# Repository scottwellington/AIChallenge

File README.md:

# Why did the lobster blush?
###### Because the sugar kelp.

---

Welcome to Team 1's GitHub for the AI Challenge!

---

## Getting started

**Step 1**: Grab [Git] tools(https://git-scm.com/book/en/v2/Getting-Started-Installing-Git).

**Step 2**: Clone our repo:

`git clone https://github.com/scottwellington/AIChallenge.git`

## Notes for Team Members: making changes to this repo

Note: this is the most straight-forward and accessible way to use GitHub as a team, but this isn't how you'd typically use it: we are going to simplify the process by avoiding branches, rebase and merge, which are not newbie-friendly.

However, this requires some due diligence that you always pull the latest version before pushing any changes. Important enough to be worth repeating: *Do not push changes to the repo without first pulling the most recent version!*

Navigate to the repo (default `~/AIChallenge`)

**Step 1**: Pull the most recent version of the repo:

`git pull`

**Step 2**: Update list of md5 checksums:

`git add --all`

**Step 3**: Commit changes to your local repo, with a useful update description:

`git commit -m 'added new script for data cleaning'`

**Step 4**: Push changes to the remote repo:

`git push`

Done :-)

---

###### TODO

* 07/05/21 - go to the pub and celebrate a job well done [Scott]

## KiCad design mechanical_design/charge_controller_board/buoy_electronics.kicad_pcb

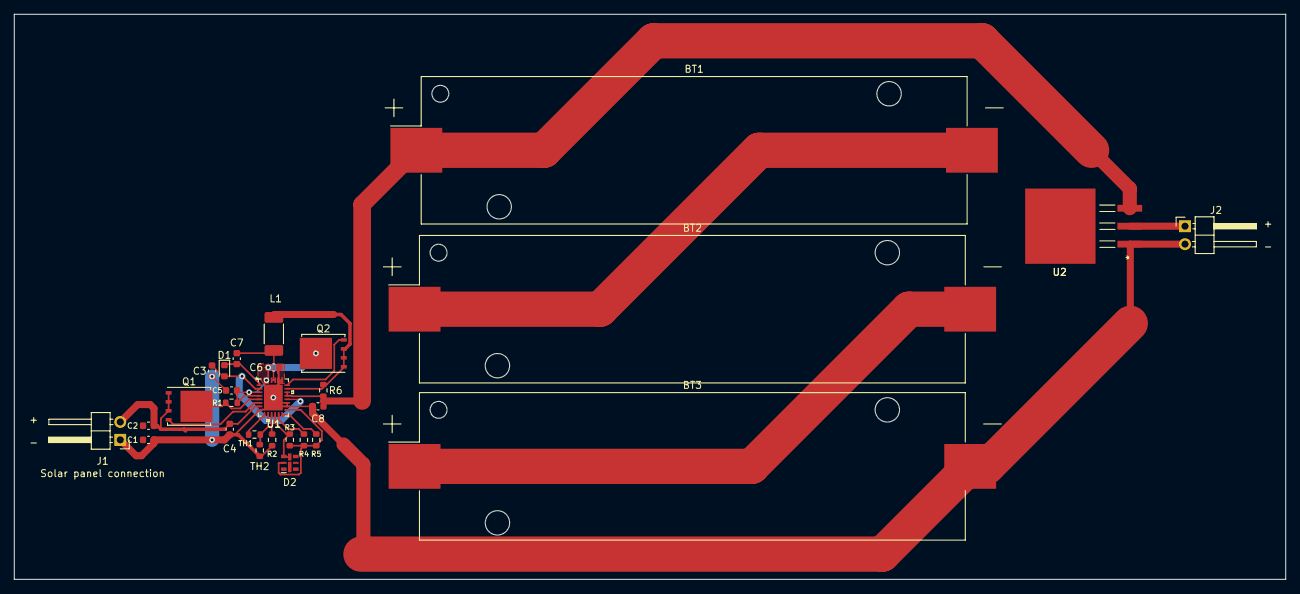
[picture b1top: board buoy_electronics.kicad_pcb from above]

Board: 2 copper layers, 180.0 x 80.0 mm, 28 parts (0 on the bottom side), 22 nets.

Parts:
BT1, BT2, BT3: Battery_Cell; BatteryHolder_Keystone_1042_1x18650
C1: 2.5; C_0603_1608Metric
C2: CP1_Small; C_0603_1608Metric
C3: 4.7 uF; C_0603_1608Metric
C4, C5: 0.1 uF; C_0603_1608Metric
C6, C8: 10 uF; C_0603_1608Metric
C7: 0.022 uF; C_0603_1608Metric
D1: D_Schottky_Small_ALT; D_0603_1608Metric
D2: LED; LED-APA102-2020
J1: Conn. to solar cells; PinHeader_1x02_P2.54mm_Horizontal
J2: Conn. to Arduino; PinHeader_1x02_P2.54mm_Horizontal
L1: L_Small; L_2010_5025Metric_Pad1.52x2.65mm_HandSolder
Q1, Q2: FDMS86152; TDSON-8-1
R1: 0.016; R_0603_1608Metric
R2: 63.4k; R_0603_1608Metric
R3: 100k; R_0603_1608Metric
R4, R5: 4.7k; R_0603_1608Metric
R6: 0.01; R_0603_1608Metric
TH1, TH2: 3490K; R_0603_1608Metric
U1: U1; LTC4162EUFD
U2: U2; LM1085IS-12&slash_NOPB

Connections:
/*SMBALERT: D2.1, R3.1, U1.12
/SCL: R4.1, U1.13
/SDA: R5.1, U1.14
GND: BT3.2, C2.2, C3.2, C4.2, C5.2, C6.2, C8.2, J1.1, J2.2, R2.1, TH2.2, U1.8, U1.16, U1.17, U1.23, U1.24, U1.29, U2.1
unnamed: BT1.1, C8.1, R6.1, U1.19, U1.20, U2.3
unnamed: BT1.2, BT2.1
unnamed: BT2.2, BT3.1
unnamed: C1.1, C4.1, J1.2, Q1.1, Q1.2, Q1.3, U1.7
unnamed: C1.2, C2.1
unnamed: C5.1, C6.1, Q2.5, R1.2, U1.3, U1.4, U1.27, U1.28
unnamed: C7.1, D1.1, U1.1
unnamed: C7.2, L1.1, U1.25, U1.26
unnamed: J2.1, U2.2
unnamed: L1.2, Q2.1, Q2.2, Q2.3, R6.2, U1.21
unnamed: Q1.4, U1.6
unnamed: Q1.5, R1.1, U1.5
unnamed: Q2.4, U1.22
unnamed: R2.2, U1.11
unnamed: TH1.1, U1.9
unnamed: TH1.2, TH2.1, U1.10
VCC: C3.1, D1.2, U1.2, U1.18
VDD: D2.2, R3.2, R4.2, R5.2, U1.15

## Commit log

2021-02-22 readme update
2021-03-01 repo from paper https://www.sciencedirect.com/science/article/pii/S0960982219308863
2021-05-02 fancy graphs
2021-05-07 Prototype schematics and CAD files
2021-05-07 07/05/2021

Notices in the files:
parts and their libraries:
Copyright 2016 Accelerated Designs. All rights reserved.
